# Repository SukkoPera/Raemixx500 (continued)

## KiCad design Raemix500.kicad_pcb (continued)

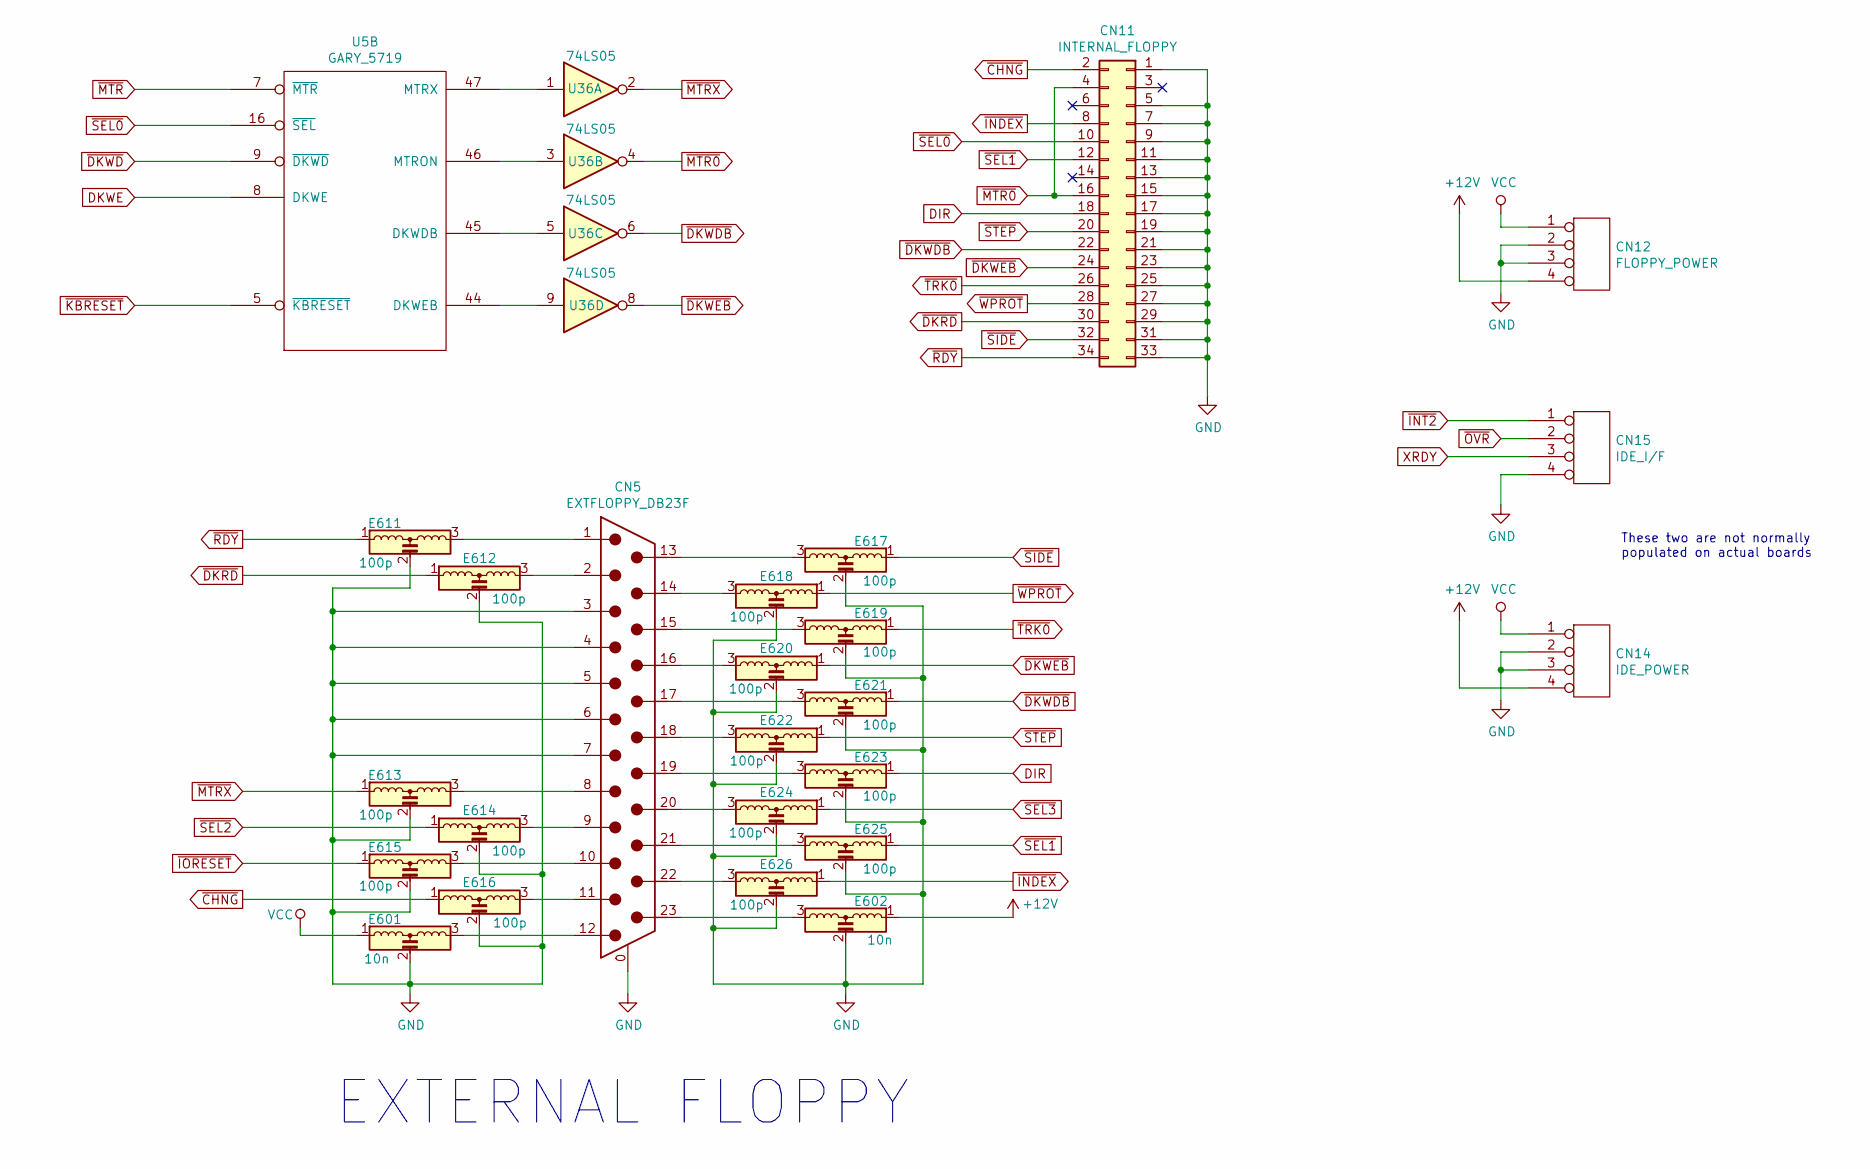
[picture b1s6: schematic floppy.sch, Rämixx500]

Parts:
CN5: EXTFLOPPY_DB23F; DB_23
CN11: INTERNAL_FLOPPY; PinHeader_2x17_P2.54mm_Vertical
CN12: FLOPPY_POWER; PinHeader_1x04_P2.54mm_Vertical
CN14: IDE_POWER; PinHeader_1x04_P2.54mm_Vertical
CN15: IDE_I/F; PinHeader_1x04_P2.54mm_Vertical
E601, E602: 10n; EMI_Filter_Long
E611, E612, E613, E614, E615, E616, E617, E618, E619, E620, E621, E622, E623, E624, E625, E626: 100p; EMI_Filter_Short
U5: GARY_5719; DIP-48_W15.24mm_Socket_LongPads
U36: 74LS05; DIP-14_W7.62mm_Socket_LongPads

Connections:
+12V: CN12.4, CN14.4, E602.1; also elsewhere on the board
DIR: CN11.18, E623.1; also elsewhere on the board
DKWE: U5.8 (DKWE); also elsewhere on the board
GND: CN5.0 (PAD), CN5.3, CN5.4, CN5.5, CN5.6, CN5.7, CN11.1, CN11.5, CN11.7, CN11.9, CN11.11, CN11.13, CN11.15, CN11.17, CN11.19, CN11.21, CN11.23, CN11.25, CN11.27, CN11.29, CN11.31, CN11.33, CN12.2, CN12.3, CN14.2, CN14.3, CN15.4, E601.2, E602.2, E611.2, E612.2, E613.2, E614.2, E615.2, E616.2, E617.2, E618.2, E619.2, E620.2, E621.2, E622.2, E623.2, E624.2, E625.2, E626.2; also elsewhere on the board
unnamed: CN5.1, E611.3
unnamed: CN5.2, E612.3
unnamed: CN5.8, E613.3
unnamed: CN5.9, E614.3
unnamed: CN5.10, E615.3
unnamed: CN5.11, E616.3
unnamed: CN5.12, E601.3
unnamed: CN5.13, E617.3
unnamed: CN5.14, E618.3
unnamed: CN5.15, E619.3
unnamed: CN5.16, E620.3
unnamed: CN5.17, E621.3
unnamed: CN5.18, E622.3
unnamed: CN5.19, E623.3
unnamed: CN5.20, E624.3
unnamed: CN5.21, E625.3
unnamed: CN5.22, E626.3
unnamed: CN5.23, E602.3
unnamed: U5.47 (MTRX), U36.1
unnamed: U5.46 (MTRON), U36.3
unnamed: U5.45 (DKWDB), U36.5
unnamed: U5.44 (DKWEB), U36.9
VCC: CN12.1, CN14.1, E601.1; also elsewhere on the board
XRDY: CN15.3; also elsewhere on the board
~CHNG: CN11.2, E616.1; also elsewhere on the board
~DKRD: CN11.30, E612.1; also elsewhere on the board
~DKWD: U5.9 (~DKWD); also elsewhere on the board
~DKWDB: CN11.22, E621.1, U36.6
~DKWEB: CN11.24, E620.1, U36.8
~INDEX: CN11.8, E626.1; also elsewhere on the board
~INT2: CN15.1; also elsewhere on the board
~IORESET: E615.1; also elsewhere on the board
~KBRESET: U5.5 (~KBRESET); also elsewhere on the board
~MTR: U5.7 (~MTR); also elsewhere on the board
~MTR0: CN11.4, CN11.16, U36.4; also elsewhere on the board
~MTRX: E613.1, U36.2
~OVR: CN15.2; also elsewhere on the board
~RDY: CN11.34, E611.1; also elsewhere on the board
~SEL0: CN11.10, U5.16 (~SEL); also elsewhere on the board
~SEL1: CN11.12, E625.1; also elsewhere on the board
~SEL2: E614.1; also elsewhere on the board
~SEL3: E624.1; also elsewhere on the board
~SIDE: CN11.32, E617.1; also elsewhere on the board
~STEP: CN11.20, E622.1; also elsewhere on the board
~TRK0: CN11.26, E619.1; also elsewhere on the board
~WPROT: CN11.28, E618.1; also elsewhere on the board

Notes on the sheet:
These two are not normally populated on actual boards
EXTERNAL FLOPPY

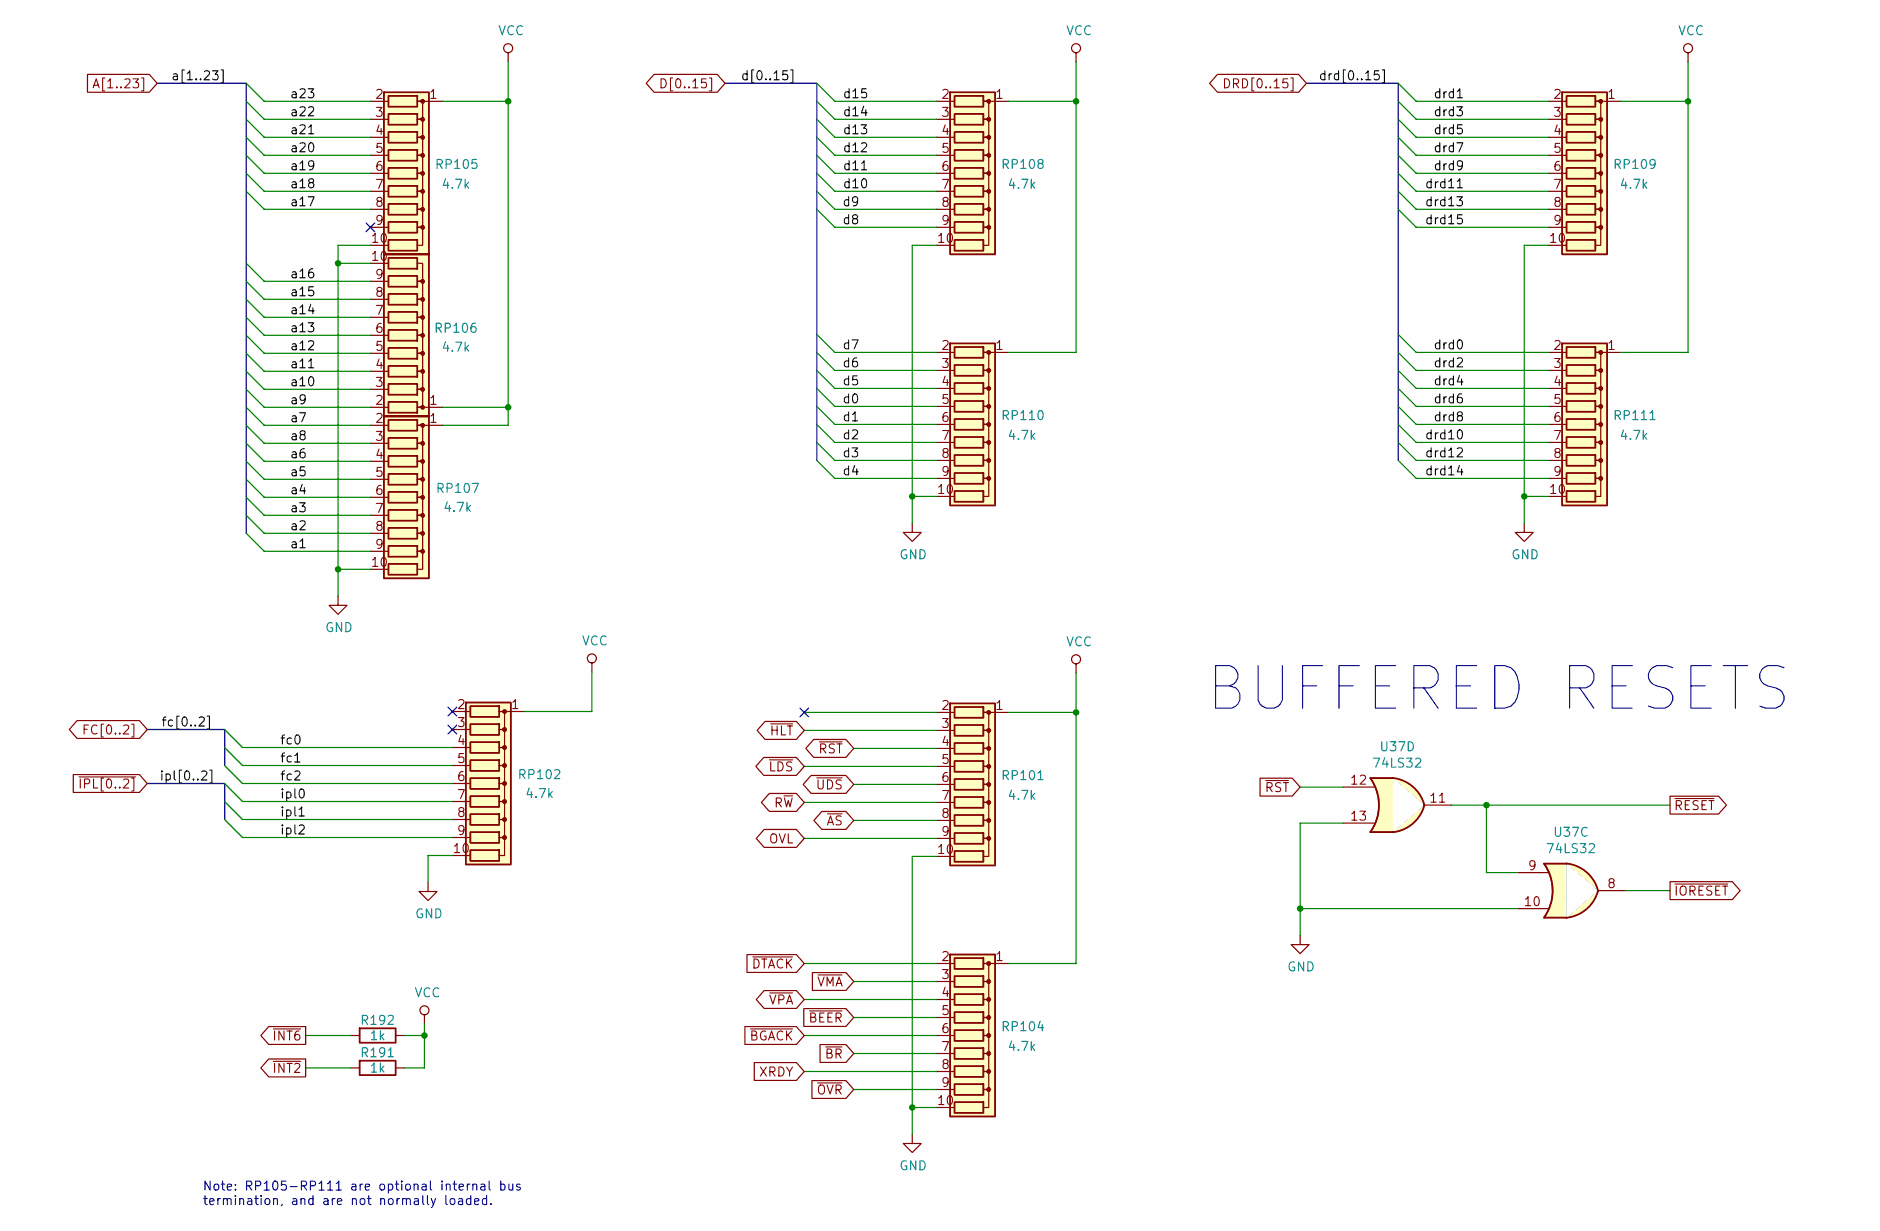
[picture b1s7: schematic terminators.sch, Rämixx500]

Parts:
R191, R192: 1k; R_Axial_DIN0309_L9.0mm_D3.2mm_P12.70mm_Horizontal
RP101, RP102, RP104, RP105, RP106, RP107, RP108, RP109, RP110, RP111: 4.7k; R_Array_SIP10
U37: 74LS32; DIP-14_W7.62mm_Socket_LongPads

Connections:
A1: RP107.9 (R8); also elsewhere on the board
A2: RP107.8 (R7); also elsewhere on the board
A3: RP107.7 (R6); also elsewhere on the board
A4: RP107.6 (R5); also elsewhere on the board
A5: RP107.5 (R4); also elsewhere on the board
A6: RP107.4 (R3); also elsewhere on the board
A7: RP107.2 (R1); also elsewhere on the board
A8: RP107.3 (R2); also elsewhere on the board
A9: RP106.2 (R1); also elsewhere on the board
A10: RP106.3 (R2); also elsewhere on the board
A11: RP106.4 (R3); also elsewhere on the board
A12: RP106.5 (R4); also elsewhere on the board
A13: RP106.6 (R5); also elsewhere on the board
A14: RP106.7 (R6); also elsewhere on the board
A15: RP106.8 (R7); also elsewhere on the board
A16: RP106.9 (R8); also elsewhere on the board
A17: RP105.8 (R7); also elsewhere on the board
A18: RP105.7 (R6); also elsewhere on the board
A19: RP105.6 (R5); also elsewhere on the board
A20: RP105.5 (R4); also elsewhere on the board
A21: RP105.4 (R3); also elsewhere on the board
A22: RP105.3 (R2); also elsewhere on the board
A23: RP105.2 (R1); also elsewhere on the board
D0: RP110.5 (R4); also elsewhere on the board
D1: RP110.6 (R5); also elsewhere on the board
D2: RP110.7 (R6); also elsewhere on the board
D3: RP110.8 (R7); also elsewhere on the board
D4: RP110.9 (R8); also elsewhere on the board
D5: RP110.4 (R3); also elsewhere on the board
D6: RP110.3 (R2); also elsewhere on the board
D7: RP110.2 (R1); also elsewhere on the board
D8: RP108.9 (R8); also elsewhere on the board
D9: RP108.8 (R7); also elsewhere on the board
D10: RP108.7 (R6); also elsewhere on the board
D11: RP108.6 (R5); also elsewhere on the board
D12: RP108.5 (R4); also elsewhere on the board
D13: RP108.4 (R3); also elsewhere on the board
D14: RP108.3 (R2); also elsewhere on the board
D15: RP108.2 (R1); also elsewhere on the board
DRD0: RP111.2 (R1); also elsewhere on the board
DRD1: RP109.2 (R1); also elsewhere on the board
DRD2: RP111.3 (R2); also elsewhere on the board
DRD3: RP109.3 (R2); also elsewhere on the board
DRD4: RP111.4 (R3); also elsewhere on the board
DRD5: RP109.4 (R3); also elsewhere on the board
DRD6: RP111.5 (R4); also elsewhere on the board
DRD7: RP109.5 (R4); also elsewhere on the board
DRD8: RP111.6 (R5); also elsewhere on the board
DRD9: RP109.6 (R5); also elsewhere on the board
DRD10: RP111.7 (R6); also elsewhere on the board
DRD11: RP109.7 (R6); also elsewhere on the board
DRD12: RP111.8 (R7); also elsewhere on the board
DRD13: RP109.8 (R7); also elsewhere on the board
DRD14: RP111.9 (R8); also elsewhere on the board
DRD15: RP109.9 (R8); also elsewhere on the board
FC0: RP102.4 (R3); also elsewhere on the board
FC1: RP102.5 (R4); also elsewhere on the board
FC2: RP102.6 (R5); also elsewhere on the board
GND: RP101.10 (R9), RP102.10 (R9), RP104.10 (R9), RP105.10 (R9), RP106.10 (R9), RP107.10 (R9), RP108.10 (R9), RP109.10 (R9), RP110.10 (R9), RP111.10 (R9), U37.10, U37.13; also elsewhere on the board
OVL: RP101.9 (R8); also elsewhere on the board
R~W: RP101.7 (R6); also elsewhere on the board
VCC: R191.1, R192.1, RP101.1 (common), RP102.1 (common), RP104.1 (common), RP105.1 (common), RP106.1 (common), RP107.1 (common), RP108.1 (common), RP109.1 (common), RP110.1 (common), RP111.1 (common); also elsewhere on the board
XRDY: RP104.8 (R7); also elsewhere on the board
~AS: RP101.8 (R7); also elsewhere on the board
~BEER: RP104.5 (R4); also elsewhere on the board
~BGACK: RP104.6 (R5); also elsewhere on the board
~BR: RP104.7 (R6); also elsewhere on the board
~DTACK: RP104.2 (R1); also elsewhere on the board
~HLT: RP101.3 (R2); also elsewhere on the board
~INT2: R191.2; also elsewhere on the board
~INT6: R192.2; also elsewhere on the board
~IORESET: U37.8; also elsewhere on the board
~IPL0: RP102.7 (R6); also elsewhere on the board
~IPL1: RP102.8 (R7); also elsewhere on the board
~IPL2: RP102.9 (R8); also elsewhere on the board
~LDS: RP101.5 (R4); also elsewhere on the board
~OVR: RP104.9 (R8); also elsewhere on the board
~RESET: U37.9, U37.11; also elsewhere on the board
~RST: RP101.4 (R3), U37.12; also elsewhere on the board
~UDS: RP101.6 (R5); also elsewhere on the board
~VMA: RP104.3 (R2); also elsewhere on the board
~VPA: RP104.4 (R3); also elsewhere on the board

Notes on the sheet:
Note: RP105-RP111 are optional internal bus termination, and are not normally loaded.
BUFFERED RESETS

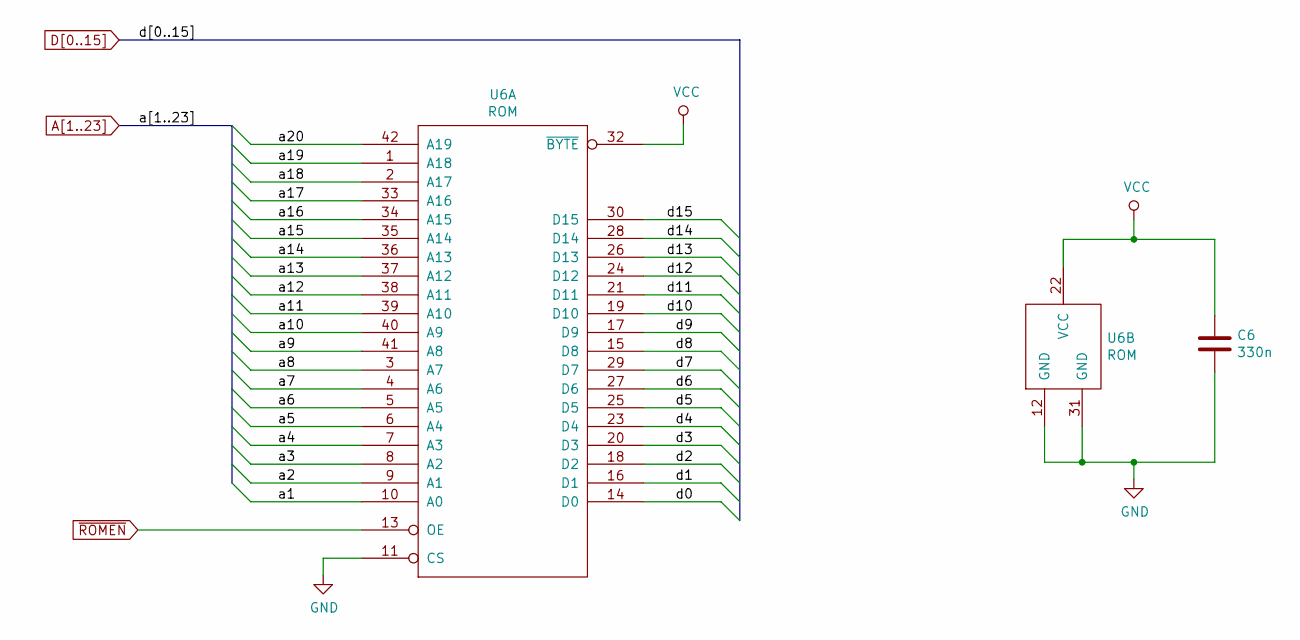
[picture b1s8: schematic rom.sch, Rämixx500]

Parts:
C6: 330n; C_Axial_L6.3mm_D2.5mm_P10.16mm
U6: ROM; DIP-42_W15.24mm_Socket_LongPads

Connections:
A1: U6.10 (A0); also elsewhere on the board
A2: U6.9 (A1); also elsewhere on the board
A3: U6.8 (A2); also elsewhere on the board
A4: U6.7 (A3); also elsewhere on the board
A5: U6.6 (A4); also elsewhere on the board
A6: U6.5 (A5); also elsewhere on the board
A7: U6.4 (A6); also elsewhere on the board
A8: U6.3 (A7); also elsewhere on the board
A9: U6.41 (A8); also elsewhere on the board
A10: U6.40 (A9); also elsewhere on the board
A11: U6.39 (A10); also elsewhere on the board
A12: U6.38 (A11); also elsewhere on the board
A13: U6.37 (A12); also elsewhere on the board
A14: U6.36 (A13); also elsewhere on the board
A15: U6.35 (A14); also elsewhere on the board
A16: U6.34 (A15); also elsewhere on the board
A17: U6.33 (A16); also elsewhere on the board
A18: U6.2 (A17); also elsewhere on the board
A19: U6.1 (A18); also elsewhere on the board
A20: U6.42 (A19); also elsewhere on the board
D0: U6.14 (D0); also elsewhere on the board
D1: U6.16 (D1); also elsewhere on the board
D2: U6.18 (D2); also elsewhere on the board
D3: U6.20 (D3); also elsewhere on the board
D4: U6.23 (D4); also elsewhere on the board
D5: U6.25 (D5); also elsewhere on the board
D6: U6.27 (D6); also elsewhere on the board
D7: U6.29 (D7); also elsewhere on the board
D8: U6.15 (D8); also elsewhere on the board
D9: U6.17 (D9); also elsewhere on the board
D10: U6.19 (D10); also elsewhere on the board
D11: U6.21 (D11); also elsewhere on the board
D12: U6.24 (D12); also elsewhere on the board
D13: U6.26 (D13); also elsewhere on the board
D14: U6.28 (D14); also elsewhere on the board
D15: U6.30 (D15); also elsewhere on the board
GND: C6.2, U6.11 (CS), U6.12 (GND), U6.31 (GND); also elsewhere on the board
VCC: C6.1, U6.22 (VCC), U6.32 (~BYTE); also elsewhere on the board
~ROMEN: U6.13 (OE); also elsewhere on the board

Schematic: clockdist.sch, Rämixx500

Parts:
C33: 10n; C_Axial_L6.3mm_D2.5mm_P10.16mm
E102, E103, E106, E107, E108: 47p; C_Axial_L9.0mm_D3.2mm_P12.70mm
E104, E105: 68; EMI_Filter_Long
E109, E791, E792, E793, E794: 47p; C_Axial_L6.3mm_D2.5mm_P10.16mm
E407: 10n; EMI_Filter_Short
RP103: 39; R_Array_SIP10
U33: 74LS258; DIP-16_W7.62mm_Socket_LongPads

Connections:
7MHZ: E103.1; also elsewhere on the board
7MHZ_A: E794.1; also elsewhere on the board
CCK: E108.1, U33.5, U33.6; also elsewhere on the board
CCKQ: E107.1, U33.10, U33.11; also elsewhere on the board
CDAC: E793.1, RP103.4 (R2.2); also elsewhere on the board
GND: C33.2, E102.2, E103.2, E104.2, E105.2, E106.2, E107.2, E108.2, E109.2, E407.2, E791.2, E792.2, E793.2, E794.2, U33.8 (GND), U33.15 (OE); also elsewhere on the board
unnamed: C33.1, E407.3, U33.16 (VCC)
unnamed: E104.1, RP103.5 (R3.1), U33.7
unnamed: E105.1, RP103.7 (R4.1), U33.9
unnamed: RP103.3 (R2.1), U33.4
VCC: E407.1; also elsewhere on the board
~CCK: E792.1, RP103.6 (R3.2); also elsewhere on the board
~CCKQ: E791.1, RP103.8 (R4.2); also elsewhere on the board
~CCKQ_A: E105.3, E109.1; also elsewhere on the board
~CCK_A: E102.1, E104.3; also elsewhere on the board
~CDAC: E106.1, U33.2, U33.3; also elsewhere on the board

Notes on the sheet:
FCC GOOBERS

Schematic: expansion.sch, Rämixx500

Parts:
E702, E703, E704: 10n; EMI_Filter_Short
P1: EXPANSION BUS; A2000_COPRO_SLOT

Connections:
7MHZ: P1.7 (PIN7); also elsewhere on the board
+12V: E704.1; also elsewhere on the board
-12V: E703.1; also elsewhere on the board
A1: P1.29 (PIN29); also elsewhere on the board
A2: P1.27 (PIN27); also elsewhere on the board
A3: P1.26 (PIN26); also elsewhere on the board
A4: P1.24 (PIN24); also elsewhere on the board
A5: P1.21 (PIN21); also elsewhere on the board
A6: P1.23 (PIN23); also elsewhere on the board
A7: P1.28 (PIN28); also elsewhere on the board
A8: P1.30 (PIN30); also elsewhere on the board
A9: P1.32 (PIN32); also elsewhere on the board
A10: P1.34 (PIN34); also elsewhere on the board
A11: P1.36 (PIN36); also elsewhere on the board
A12: P1.38 (PIN38); also elsewhere on the board
A13: P1.39 (PIN39); also elsewhere on the board
A14: P1.41 (PIN41); also elsewhere on the board
A15: P1.43 (PIN43); also elsewhere on the board
A16: P1.45 (PIN45); also elsewhere on the board
A17: P1.47 (PIN47); also elsewhere on the board
A18: P1.52 (PIN52); also elsewhere on the board
A19: P1.54 (PIN54); also elsewhere on the board
A20: P1.56 (PIN56); also elsewhere on the board
A21: P1.58 (PIN58); also elsewhere on the board
A22: P1.57 (PIN57); also elsewhere on the board
A23: P1.59 (PIN59); also elsewhere on the board
CDAC: P1.15 (PIN15); also elsewhere on the board
D0: P1.75 (PIN75); also elsewhere on the board
D1: P1.77 (PIN77); also elsewhere on the board
D2: P1.79 (PIN79); also elsewhere on the board
D3: P1.81 (PIN81); also elsewhere on the board
D4: P1.83 (PIN83); also elsewhere on the board
D5: P1.86 (PIN86); also elsewhere on the board
D6: P1.84 (PIN84); also elsewhere on the board
D7: P1.82 (PIN82); also elsewhere on the board
D8: P1.80 (PIN80); also elsewhere on the board
D9: P1.78 (PIN78); also elsewhere on the board
D10: P1.76 (PIN76); also elsewhere on the board
D11: P1.71 (PIN71); also elsewhere on the board
D12: P1.69 (PIN69); also elsewhere on the board
D13: P1.67 (PIN67); also elsewhere on the board
D14: P1.65 (PIN65); also elsewhere on the board
D15: P1.63 (PIN63); also elsewhere on the board
E: P1.50 (PIN50); also elsewhere on the board
FC0: P1.31 (PIN31); also elsewhere on the board
FC1: P1.33 (PIN33); also elsewhere on the board
FC2: P1.35 (PIN35); also elsewhere on the board
GND: E702.2, E703.2, E704.2, P1.1 (PIN1), P1.2 (PIN2), P1.3 (PIN3), P1.4 (PIN4), P1.13 (PIN13), P1.25 (PIN25), P1.37 (PIN37), P1.49 (PIN49), P1.61 (PIN61), P1.73 (PIN73), P1.85 (PIN85); also elsewhere on the board
unnamed: E702.3, P1.5 (PIN5), P1.6 (PIN6), P1.12 (PIN12)
unnamed: E703.3, P1.8 (PIN8)
unnamed: E704.3, P1.10 (PIN10)
R~W: P1.68 (PIN68); also elsewhere on the board
VCC: E702.1; also elsewhere on the board
XRDY: P1.18 (PIN18); also elsewhere on the board
~AS: P1.74 (PIN74); also elsewhere on the board
~BEER: P1.46 (PIN46); also elsewhere on the board
~BG: P1.64 (PIN64); also elsewhere on the board
~BGACK: P1.62 (PIN62); also elsewhere on the board
~BR: P1.60 (PIN60); also elsewhere on the board
~CCK: P1.16 (PIN16); also elsewhere on the board
~CCKQ: P1.14 (PIN14); also elsewhere on the board
~DTACK: P1.66 (PIN66); also elsewhere on the board
~HLT: P1.55 (PIN55); also elsewhere on the board
~INT2: P1.19 (PIN19); also elsewhere on the board
~INT6: P1.22 (PIN22); also elsewhere on the board
~IPL0: P1.40 (PIN40); also elsewhere on the board
~IPL1: P1.42 (PIN42); also elsewhere on the board
~IPL2: P1.44 (PIN44); also elsewhere on the board
~LDS: P1.70 (PIN70); also elsewhere on the board
~OVR: P1.17 (PIN17); also elsewhere on the board
~RST: P1.53 (PIN53); also elsewhere on the board
~UDS: P1.72 (PIN72); also elsewhere on the board
~VMA: P1.51 (PIN51); also elsewhere on the board
~VPA: P1.48 (PIN48); also elsewhere on the board

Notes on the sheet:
~CONFIG

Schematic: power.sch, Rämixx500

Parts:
C1, C2, C5, C11, C13, C14, C804: 330n; C_Axial_L6.3mm_D2.5mm_P10.16mm
C10, C12, C32, C34, C35, C36, C37, C701, C800, C801, C802, C803: 10n; C_Axial_L6.3mm_D2.5mm_P10.16mm
C811, C812, C813, C814, C815, C816: 100u; CP_Radial_D8.0mm_P5.00mm
C821, C822: 47u; CP_Radial_D8.0mm_P5.00mm
CN8: Power_Conn; din-5
E101, E110: 10n; EMI_Filter_Short
LF1: L; LineFilter
MT1, MT2, MT4, MT5, MT6, MT7: MountingHole_Pad; MountingHole_4mm_Pad
U1: 68000D; DIP-64_W22.86mm_Socket_LongPads
U2: FAT_AGNUS_8375; PLCC-84_THT-Socket
U5: GARY_5719; DIP-48_W15.24mm_Socket_LongPads
U10, U12, U35: 74LS244; DIP-20_W7.62mm_Socket_LongPads
U11, U13, U34: 74LS373; DIP-20_W7.62mm_Socket_LongPads
U32: 74LS139; DIP-16_W7.62mm_Socket_LongPads
U36: 74LS05; DIP-14_W7.62mm_Socket_LongPads
U37: 74LS32; DIP-14_W7.62mm_Socket_LongPads
X1: XTAL; Xtal

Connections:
+12V: C802.1, C821.1, LF1.5; also elsewhere on the board
-12V: C803.2, C822.2, LF1.6; also elsewhere on the board
GND: C1.2, C2.2, C5.2, C10.2, C11.2, C12.2, C13.2, C14.2, C32.2, C34.2, C35.2, C36.2, C37.2, C701.2, C801.2, C802.2, C803.1, C804.2, C811.2, C812.2, C813.2, C814.2, C815.2, C816.2, C821.2, C822.1, CN8.2 (SH1), CN8.6 (SH2), E101.2, E110.2, LF1.8, MT1.1, MT2.1, MT4.1, MT5.1, MT6.1, MT7.1, U1.16 (GND), U1.53 (GND), U2.41 (GND), U2.58 (GND), U2.82 (GND), U5.1 (GND), U5.24 (GND), U5.40 (GND), U10.10 (GND), U11.10 (GND), U12.10 (GND), U13.10 (GND), U32.8 (GND), U34.10 (GND), U35.10 (GND), U36.7 (GND), U37.7 (GND), X1.1 (~EN), X1.2 (GND); also elsewhere on the board
unnamed: C2.1, E101.3, U2.15 (VCC)
unnamed: C701.1, E110.3, X1.4 (Vdd)
unnamed: C800.1, CN8.4 (GND), LF1.1
unnamed: C800.2, CN8.1 (+5V), LF1.2
unnamed: CN8.3 (+12V), LF1.4
unnamed: CN8.5 (-12V), LF1.3
VCC: C1.1, C5.1, C10.1, C11.1, C12.1, C13.1, C14.1, C32.1, C34.1, C35.1, C36.1, C37.1, C801.1, C804.1, C811.1, C812.1, C813.1, C814.1, C815.1, C816.1, E101.1, E110.1, LF1.7, U1.14 (VCC), U1.49 (VCC), U5.6 (VCC), U5.17 (VCC), U5.48 (VCC), U10.20 (VCC), U11.20 (VCC), U12.20 (VCC), U13.20 (VCC), U32.16 (VCC), U34.20 (VCC), U35.20 (VCC), U36.14 (VCC), U37.14 (VCC); also elsewhere on the board

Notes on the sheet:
Note: This is the pinout of the MALE connector on the CABLE's end!
POWER INPUT
GROUNDED HOLES

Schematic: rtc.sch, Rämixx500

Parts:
BT9: CR2032; Battery_Holder_Coin_2032_BS-7
C9: 330n; C_Axial_L6.3mm_D2.5mm_P10.16mm
C911: 22p; C_Axial_L6.3mm_D2.5mm_P10.16mm
C913: 4.7u; CP_Radial_D8.0mm_P5.00mm
D911, D912: 1n4148; D_DO-35_SOD27_P12.70mm_Horizontal
D913: 1n5817; D_DO-41_SOD81_P12.70mm_Horizontal
JP9: Jumper_2_Open; Jumper2-Open
R911: 470; R_Axial_DIN0309_L9.0mm_D3.2mm_P12.70mm_Horizontal
R914: 10k; R_Axial_DIN0309_L9.0mm_D3.2mm_P12.70mm_Horizontal
R915, R916: 1k; R_Axial_DIN0309_L9.0mm_D3.2mm_P12.70mm_Horizontal
TC9: 6.8-45p; VariCap
U9: MSM6242B; DIP-18_W7.62mm_Socket_LongPads
U36: 74LS05; DIP-14_W7.62mm_Socket_LongPads
Y9: 32768 Hz; Crystal_RTC

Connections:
+12V: R911.2; also elsewhere on the board
A2: U9.4 (A0); also elsewhere on the board
A3: U9.5 (A1); also elsewhere on the board
A4: U9.6 (A2); also elsewhere on the board
A5: U9.7 (A3); also elsewhere on the board
A15: U36.13; also elsewhere on the board
D0: U9.14 (D0); also elsewhere on the board
D1: U9.13 (D1); also elsewhere on the board
D2: U9.12 (D2); also elsewhere on the board
D3: U9.11 (D3); also elsewhere on the board
GND: BT9.2 (-), C9.2, C911.1, C913.2, JP9.1 (A), TC9.2, U9.9 (GND); also elsewhere on the board
unnamed: BT9.1 (+), D913.2 (A)
unnamed: C9.1, C913.1, D912.1 (K), D913.1 (K), U9.18 (VCC)
unnamed: C911.2, U9.17 (~XT), Y9.3
unnamed: D911.2 (A), D912.2 (A), R911.1
unnamed: R914.2, U9.3 (ALE), U9.15 (CS1)
unnamed: R915.2, U9.2 (~CS0), U36.10
unnamed: TC9.1, U9.16 (XT), Y9.1
unnamed: U9.1 (STD.P), Y9.2
VCC: D911.1 (K), R914.1, R915.1, R916.1; also elsewhere on the board
~CLKCS: JP9.2 (B), R916.2, U36.11, U36.12; also elsewhere on the board
~CLKRD: U9.8 (~RD); also elsewhere on the board
~CLKWR: U9.10 (~WR); also elsewhere on the board

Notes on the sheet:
This diode is not installed in its place on original boards, as its cathode would connect to the other side or the resistor. But we'll fix this, so please install it normally.
This diode replaces R913 on the original schematics so that we can use a non-rechargeable battery. Use a Schottky diode to minimize the voltage drop.

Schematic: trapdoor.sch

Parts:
JP7A1: Jumper_3_Bridged12; Jumper3-Open
P9: TRAPDOOR; PinHeader_2x28_P2.54mm_Horizontal

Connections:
+12V: P9.55 (PIN55); also elsewhere on the board
-12V: P9.56 (PIN56); also elsewhere on the board
A2: P9.45 (PIN45); also elsewhere on the board
A3: P9.46 (PIN46); also elsewhere on the board
A4: P9.47 (PIN47); also elsewhere on the board
A5: P9.48 (PIN48); also elsewhere on the board
BDRA0: P9.23 (PIN23); also elsewhere on the board
BDRA1: P9.24 (PIN24); also elsewhere on the board
BDRA2: P9.25 (PIN25); also elsewhere on the board
BDRA3: P9.26 (PIN26); also elsewhere on the board
BDRA4: P9.27 (PIN27); also elsewhere on the board
BDRA5: P9.28 (PIN28); also elsewhere on the board
BDRA6: P9.29 (PIN29); also elsewhere on the board
BDRA7: P9.30 (PIN30); also elsewhere on the board
BDRA8: P9.31 (PIN31); also elsewhere on the board
D0: P9.41 (PIN41); also elsewhere on the board
D1: P9.42 (PIN42); also elsewhere on the board
D2: P9.43 (PIN43); also elsewhere on the board
D3: P9.44 (PIN44); also elsewhere on the board
DRD0: P9.5 (PIN5); also elsewhere on the board
DRD1: P9.6 (PIN6); also elsewhere on the board
DRD2: P9.7 (PIN7); also elsewhere on the board
DRD3: P9.8 (PIN8); also elsewhere on the board
DRD4: P9.9 (PIN9); also elsewhere on the board
DRD5: P9.10 (PIN10); also elsewhere on the board
DRD6: P9.11 (PIN11); also elsewhere on the board
DRD7: P9.12 (PIN12); also elsewhere on the board
DRD8: P9.13 (PIN13); also elsewhere on the board
DRD9: P9.14 (PIN14); also elsewhere on the board
DRD10: P9.15 (PIN15); also elsewhere on the board
DRD11: P9.16 (PIN16); also elsewhere on the board
DRD12: P9.17 (PIN17); also elsewhere on the board
DRD13: P9.18 (PIN18); also elsewhere on the board
DRD14: P9.19 (PIN19); also elsewhere on the board
DRD15: P9.20 (PIN20); also elsewhere on the board
GND: JP7A1.3 (B), P9.3 (PIN3), P9.4 (PIN4), P9.21 (PIN21), P9.22 (PIN22), P9.34 (PIN34), P9.53 (PIN53), P9.54 (PIN54); also elsewhere on the board
unnamed: JP7A1.1 (A), P9.32 (PIN32)
VCC: P9.1 (PIN1), P9.2 (PIN2), P9.51 (PIN51), P9.52 (PIN52); also elsewhere on the board
~BCASL1: P9.35 (PIN35); also elsewhere on the board
~BCASU1: P9.36 (PIN36); also elsewhere on the board
~BRAS0: P9.38 (PIN38); also elsewhere on the board
~BRAS1: P9.37 (PIN37); also elsewhere on the board
~BWE: P9.39 (PIN39); also elsewhere on the board
~CCK_A: P9.40 (PIN40); also elsewhere on the board
~CLKCS: P9.33 (PIN33); also elsewhere on the board
~CLKRD: P9.49 (PIN49); also elsewhere on the board
~CLKWR: P9.50 (PIN50); also elsewhere on the board
~EXTICK: JP7A1.2 (C); also elsewhere on the board

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
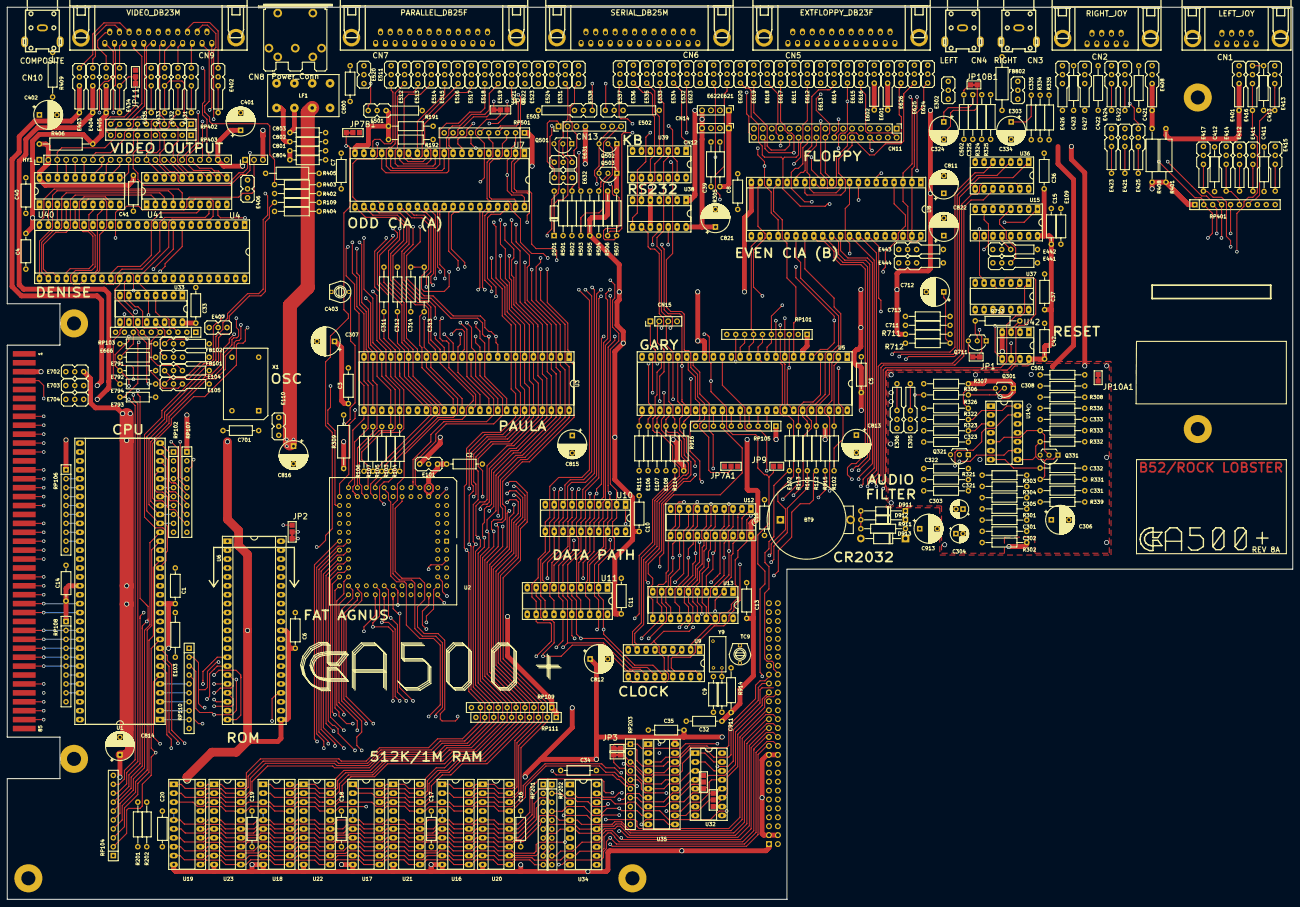
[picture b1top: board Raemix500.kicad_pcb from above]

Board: 2 copper layers, 366.0 x 254.0 mm, 349 parts (1 on the bottom side), 459 nets.

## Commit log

2019-04-14 Initial commit of this crazy project
2019-04-14 Add Denise & Video
2019-04-15 Add Paula and Joystick Ports, audio filters still missing
2019-04-15 Add Agnus VBB cap value
2019-04-15 Add audio filters
2019-04-16 Rename audio schematics
2019-04-16 Add CIAs, Parallel port and part of Serial port
2019-04-17 Complete Serial port
2019-04-17 Add missing library
2019-04-17 Add keyboard connector
2019-04-17 Add power-on reset
2019-04-17 Add floppy stuff, not yet complete
2019-04-18 Fix some references
2019-04-20 Add terminators and ROM, fix bus interconnections
2019-04-20 Add clock distribution
2019-04-20 Add main crystal
2019-04-20 Fix some symbols
2019-04-20 Add video power
2019-04-20 Add expansion bus
2019-04-20 Add power & decoupling, not yet complete
2019-04-23 Add power input and complete clock distribution
2019-04-23 Add RTC
2019-04-23 Add trapdoor connector
2019-04-24 Replace RAM with original design
2019-05-01 Complete RAM
2019-05-01 Fix some RAM signals
2019-05-01 Add images with quotes (Thanks @screwbreaker!)
2019-05-02 Add external floppy connector (and do a few fixes)
2019-05-02 Add composite output
2019-05-07 Add work-in-progress PCB
2019-05-07 Add gp-lib-table
2019-05-07 Work on RAM
2019-05-07 Work in progress
2019-05-07 Fix Bridged Jumper footprint
2019-05-07 Fix power-up reset
2019-05-08 Add fp-info-cache
2019-05-08 Work on joystick ports
2019-05-08 Work on odd CIA
2019-05-09 Almost all components positioned
2019-05-12 Top layer done!
2019-05-12 Add some missing tracks
2019-05-13 Add some labels and improve AGND/GND separation
2019-05-13 Remove templates
2019-05-13 Place RP109/111 better
2019-05-13 Add some tracks that got lost
2019-05-13 Begun work on bottom layer
2019-06-23 Almost there :)
2019-06-23 Looks like all tracks are connected!
2019-06-23 Complete top audio ground and fix some mistakes
2019-06-23 Fix important DRC errors
2019-06-23 Fix expansion connector
2019-06-23 Erm, fix expansion connector grounds
2019-06-23 Fix via
2019-06-23 Fix 3D model a bit
2019-06-23 Fix shielding of D-Sub connectors
2019-06-23 Fix bottom audio ground
2019-07-22 Fix typo
2019-07-22 Wire Power Connector (Original+DIN-5)
2019-07-22 Fix power connector label
2019-07-22 Fix keyboard connector key pin
2019-07-22 Add C99 on PCB
2019-11-07 Add (hopefully) all vias between ground layers
2019-11-09 Add missing via in audio ground section
2020-04-04 Add fp-info-cache to .gitignore
2020-04-04 Remove fp-info-cache
2020-04-04 Fix a lot of ERC/DRC errors
2020-04-04 Fix misaligned pad on expansion connector
2020-04-04 Replace audio/composite jacks with A600's - This means PCB IS READY! Still need to fix the silkscreen though...
2020-04-05 Use KiCad footprint for oscillator
2020-04-05 Use proper trapdoor footprint at last
2020-04-05 Switch back to SOD27 footprint for D913
2020-04-05 Avoid battery holder crashing into C12
2020-04-05 Add some 3D models
2020-04-05 Fix JP7A/B
2020-04-05 Erm, *actually* fix JP7A
2020-04-05 Some minor fixes here and there
2020-04-05 Start polishing silkscreen; all ICs and connectors done
2020-04-05 Minor fixes here and there
2020-04-05 Even some more
2020-04-06 Mooooore and more minor fixes
2020-04-06 Work on silkscreen and some minor fixes
2020-04-11 Almost ready for V1
2020-04-11 Add OSHW & KiCad logos
2020-04-11 Remove stray via
2020-04-11 Minor fixes
2020-04-11 Add logos and credits
2020-04-11 Make corners round
2020-04-11 Add renders
2020-04-11 Erm, fix a huge mistake in the audio part and some refinements
2020-04-11 Minor corrections
2020-04-12 Raemix500 -> Raemixx500
2020-04-12 Ready for V1
2020-04-12 Fix render names
2020-04-14 Add license PDF & Co.
2020-04-15 Add some info and fix PCBWay board link
2020-04-18 Redo power connector and some cosmetic fixes here and there
2020-04-18 Fix wrong symbols in schematics - Does not impact PCB
2020-04-19 Begin adding part numbers
2020-04-19 More part numbers
2020-04-19 Use 12.5mm footprints for C401/2 - Closes #16
2020-04-19 Use D12.5mm for C307 as well
2020-04-19 Guess what???
2020-04-19 Add EMI filter types
2020-04-23 Fix jumpers, which fixes ERC down to 0 errors! Yay!
2020-04-23 Add part numbers for EMI filters Not the original filters, but what seem to be suitable replacements available today
2020-04-23 Missing comma
2020-04-23 Fix note on JP4A/B
2020-04-23 Fix note on power connector
2020-04-23 Typo
2020-04-26 Add EMI filter 3D models, add logo, re-add Rock Lobster (closes #15) Thanks to Szabó Zoltán and Workshopshed!
2020-04-26 Make DSS 3d model slightly narrower, add E501/2/3
2020-04-26 Add final missing 3D models Lifted from https://github.com/StormTrooper/Commodore-Plus4, thanks!
2020-04-26 Restore previous render, this one's not yet ready
2020-04-26 V1 -> V1B (not ready yet)
2020-04-26 Use full IDC connector for floppy and some cosmetic fixes
2020-05-01 Cosmetic fixes and add missing (but harmless) track
2020-05-01 More cosmetic fixes
2020-05-01 Rework JP10A
2020-05-01 Increase ground fill clearance
2020-05-02 Moooooore cosmetic fixes
2020-05-02 Use alternative logo And sorry, just realized I forgot to commit it...
2020-05-02 Make C712 footprint smaller
2020-05-02 Final cosmetic touches
2020-05-02 Add drive switcher
2020-05-02 Add Kickstart switcher
2020-05-02 More polishing
2020-05-02 Finalize ground fills
2020-05-02 It's never enough
2020-05-02 I'm tired and I want to go to bed
2020-05-02 I had a little drink about an hour ago
2020-05-02 Don't stooop meee nooooooooooow
2021-01-03 Fix the path of some 3D models - Closes #19
2021-01-03 Change 3D model of parallel port to female
2021-06-20 (Try to) Identify the minimum set of required components
2021-06-20 Make tracks more even (?)
2021-06-20 Rename "Optional" Field to "Section"
2021-06-20 Switch to the CC BY-NC-SA 4.0 License Please note that COMMERCIAL USE OF THIS WORK IS PROHIBITED starting from this commit, except as stated in the README.
2021-06-20 Add labels on all resistors, caps and ICs + More work on silkscreen
2021-06-20 Add alternative footprint for modern equivalent of line filter
2021-06-20 Make ground plane (slightly) less intrusive
2021-06-20 Add ESD protection on joystick/mouse ports
2021-06-20 Restore Line Filter 3D model
2021-06-20 Make pin holes for DB-23 connectors 1.2mm in diameter This is because the original DB-23 connectors used by Commodore seem to have thicker pins
2021-06-20 Add credits for KINMAMI
2021-06-20 Add ground track between HSYNC and VSYNC to avoid inducted noise
2021-06-20 Fix via in wrong place
2021-06-20 Add alternative SMT footprints for Q321/331
2021-06-20 Add optional buffer for HSYNC/VSYNC
2021-06-20 RP104 -> 470R
2021-06-20 Reposition some ground vias
2021-06-20 Add connector to blink the Floppy LED on HD activity
2021-06-20 Lotsa fine-tuning
2021-06-20 Final touches for V2A
2021-06-20 Add missing connection (Thanks @LIV2!)
2021-06-20 Add model on silkscreen for SMD ICs
2021-06-20 Replace OSHW logo with CC-BY-NC-SA logo - Ready for V2B Sigh.
2021-06-20 Make dimensions the *very* same as the original board and (try to) place connectors better This was a HUUUUUUUUUUUGE work, hopefully we didn't break anything and the joystick ports will now fit bette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
2021-06-20 Add RTC crystal frequency on silkscreen
2021-06-20 Ready for V2B2
2021-06-20 Final touches for V2
2021-06-20 Some more work on silkscreen
2021-06-20 More fine-tuning...
2021-06-20 Restore ground plane on left edge and near trapdoor
2021-06-20 Fix some interruptions in ground plane
2021-06-20 Fix a few tracks that have always bothered me
2021-12-13 Update README for release
2021-12-13 Remove leftover file
2021-12-15 Add link to sordan.ie
2021-12-15 Add IC 3D models and update render
2021-12-21 Update board link
